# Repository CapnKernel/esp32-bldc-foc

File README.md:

# esp32-bldc-foc
A clone of the MKS ESP32-based FOC BLDC driver

Originally found here:

  https://github.com/makerbase-motor/MKS-ESP32FOC

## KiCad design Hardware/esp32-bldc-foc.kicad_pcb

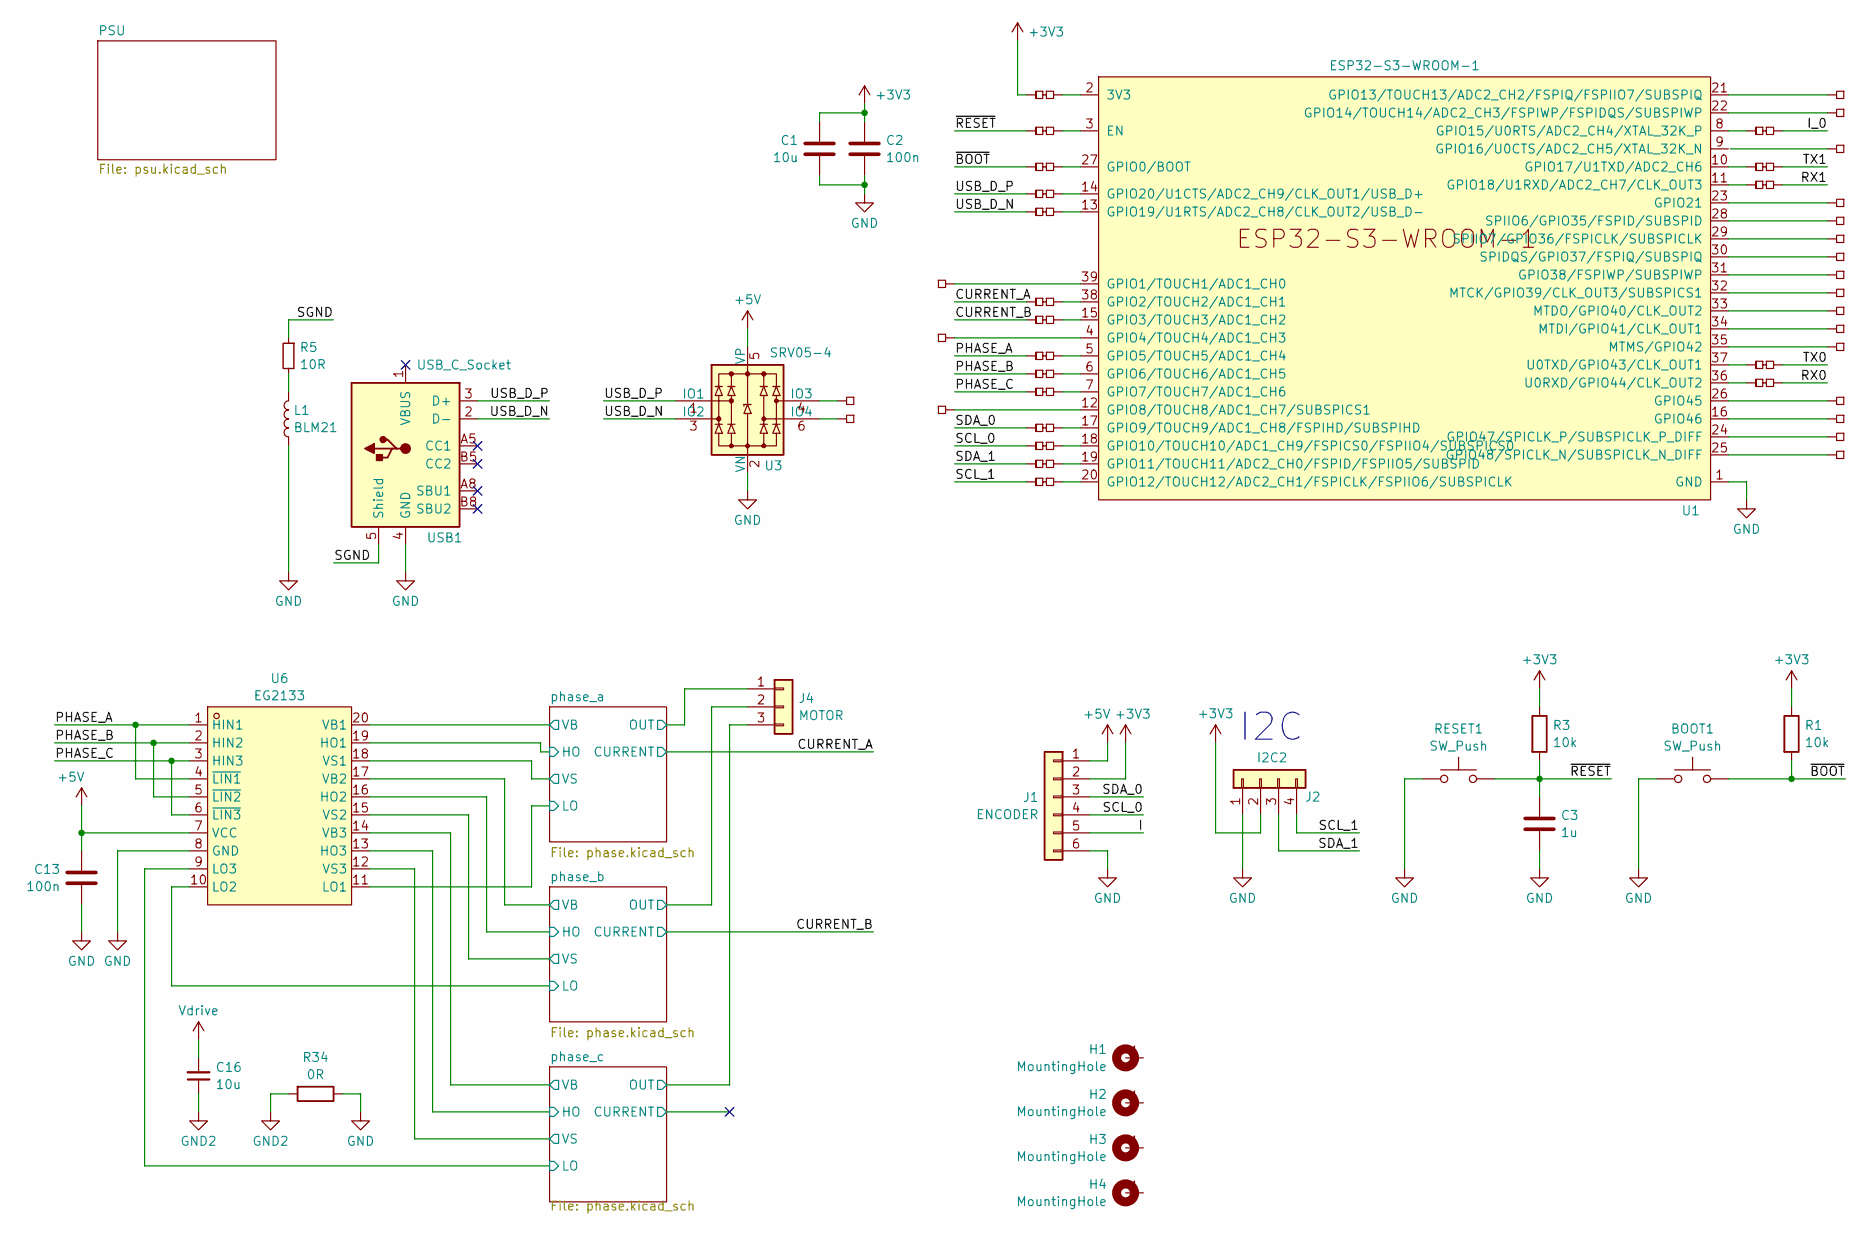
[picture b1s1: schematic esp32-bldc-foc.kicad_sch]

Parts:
BOOT1: SW_Push; SW_Push_SPST_NO_432
C1: 10u; C_0805_2012Metric
C2, C13: 100n; C_0603_1608Metric
C3: 1u; C_0603_1608Metric
C16: 10u; C_1206_3216Metric
H1, H2, H3, H4: MountingHole; MountingHole_3.2mm_M3_Pad
J1: ENCODER; PinSocket_1x06_P2.54mm_Vertical
J2: I2C2; JST_SH_SM04B-SRSS-TB_1x04-1MP_P1.00mm_Horizontal
J4: MOTOR; TerminalBlock_MetzConnect_Type094_RT03503HBLU_1x03_P5.00mm_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
L1: BLM21; L_0603_1608Metric
P1, P2, P3, P4, P5, P6, P7, P8, P9, P10, P11, P12, P13, P14, P15, P16, P17, P18, P19, P20, P21: PCB_Pin_Breakout; tinySJ-Testpoint-0.7mm
P22, P23, P24, P25, P26, P27, P28, P29, P30, P31, P32, P33, P34, P35, P36, P37, P38, P39, P40: PCB_Patch; tinySJ-Bridged
R1, R3: 10k; R_0603_1608Metric
R5: 10R; R_0603_1608Metric
R34: 0R; R_0805_2012Metric
RESET1: SW_Push; SW_Push_SPST_NO_432
U1: ESP32-S3-WROOM-1
U3: SRV05-4; SOT-23-6
U6: EG2133; TSSOP-20_L6.5-W4.4-P0.65-LS6.4-BL; LCSC C190343
USB1: USB_C_Socket; Tinker-USB_C; LCSC C2765186

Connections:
+3V3: C1.1, C2.1, J1.2, J2.2, P40.1, R1.1, R3.1; also elsewhere on the board
+5V: C13.2, J1.1, U3.5 (VP), U6.7 (VCC); also elsewhere on the board
/CURRENT_A: P26.1; also elsewhere on the board
/CURRENT_B: P27.1; also elsewhere on the board
/I: J1.5
/I_0: P35.2
/PHASE_A: P28.1, U6.1 (HIN1), U6.4 (~LIN1)
/PHASE_B: P29.1, U6.2 (HIN2), U6.5 (~LIN2)
/PHASE_C: P30.1, U6.3 (HIN3), U6.6 (~LIN3)
/RX0: P39.2
/RX1: P37.2
/SCL_0: J1.4, P32.1
/SCL_1: J2.4, P34.1
/SDA_0: J1.3, P31.1
/SDA_1: J2.3, P33.1
/SGND: R5.1, USB1.5 (Shield)
/TX0: P38.2
/TX1: P36.2
/USB_D_N: P25.1, U3.3 (IO2), USB1.2 (D-)
/USB_D_P: P24.1, U3.1 (IO1), USB1.3 (D+)
/phase_a/HO: U6.19 (HO1); also elsewhere on the board
/phase_a/LO: U6.11 (LO1); also elsewhere on the board
/phase_a/OUT: J4.1; also elsewhere on the board
/phase_a/VB: U6.20 (VB1); also elsewhere on the board
/phase_a/VS: U6.18 (VS1); also elsewhere on the board
/phase_b/HO: U6.16 (HO2); also elsewhere on the board
/phase_b/LO: U6.10 (LO2); also elsewhere on the board
/phase_b/OUT: J4.2; also elsewhere on the board
/phase_b/VB: U6.17 (VB2); also elsewhere on the board
/phase_b/VS: U6.15 (VS2); also elsewhere on the board
/phase_c/HO: U6.13 (HO3); also elsewhere on the board
/phase_c/LO: U6.9 (LO3); also elsewhere on the board
/phase_c/OUT: J4.3; also elsewhere on the board
/phase_c/VB: U6.14 (VB3); also elsewhere on the board
/phase_c/VS: U6.12 (VS3); also elsewhere on the board
/~BOOT: BOOT1.2, P23.1, R1.2
/~RESET: C3.1, P22.1, R3.2, RESET1.2
GND: BOOT1.1, C1.2, C2.2, C3.2, C13.1, J1.6, J2.1, L1.2, R34.1, RESET1.1, U1.1 (GND), U1.40 (GND), U1.41 (GND), U3.2 (VN), U6.8 (GND), USB1.4 (GND); also elsewhere on the board
GND2: C16.1, R34.2; also elsewhere on the board
unnamed: L1.1, R5.2
unnamed: P40.2, U1.2 (3V3)
unnamed: P22.2, U1.3 (EN)
unnamed: P23.2, U1.27 (GPIO0/BOOT)
unnamed: P1.1, U1.39 (GPIO1/TOUCH1/ADC1_CH0)
unnamed: P26.2, U1.38 (GPIO2/TOUCH2/ADC1_CH1)
unnamed: P27.2, U1.15 (GPIO3/TOUCH3/ADC1_CH2)
unnamed: P2.1, U1.4 (GPIO4/TOUCH4/ADC1_CH3)
unnamed: P28.2, U1.5 (GPIO5/TOUCH5/ADC1_CH4)
unnamed: P29.2, U1.6 (GPIO6/TOUCH6/ADC1_CH5)
unnamed: P30.2, U1.7 (GPIO7/TOUCH7/ADC1_CH6)
unnamed: P3.1, U1.12 (GPIO8/TOUCH8/ADC1_CH7/SUBSPICS1)
unnamed: P31.2, U1.17 (GPIO9/TOUCH9/ADC1_CH8/FSPIHD/SUBSPIHD)
unnamed: P32.2, U1.18 (GPIO10/TOUCH10/ADC1_CH9/FSPICS0/FSPIIO4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)
unnamed: P33.2, U1.19 (GPIO11/TOUCH11/ADC2_CH0/FSPID/FSPIIO5/S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)
unnamed: P34.2, U1.20 (GPIO12/TOUCH12/ADC2_CH1/FSPICLK/FSPIIO6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)
unnamed: P4.1, U1.21 (GPIO13/TOUCH13/ADC2_CH2/FSPIQ/FSPIIO7/S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)
unnamed: P5.1, U1.22 (GPIO14/TOUCH14/ADC2_CH3/FSPIWP/FSPIDQS/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)
unnamed: P35.1, U1.8 (GPIO15/U0RTS/ADC2_CH4/XTAL_32K_P)
unnamed: P36.1, U1.10 (GPIO17/U1TXD/ADC2_CH6)
unnamed: P37.1, U1.11 (GPIO18/U1RXD/ADC2_CH7/CLK_OUT3)
unnamed: P25.2, U1.13 (GPIO19/U1RTS/ADC2_CH8/CLK_OUT2/USB_D-)
unnamed: P24.2, U1.14 (GPIO20/U1CTS/ADC2_CH9/CLK_OUT1/USB_D+)
unnamed: P7.1, U1.23 (GPIO21)
unnamed: P11.1, U1.31 (GPIO38/FSPIWP/SUBSPIWP)
unnamed: P16.1, U1.26 (GPIO45)
unnamed: P17.1, U1.16 (GPIO46)
unnamed: P18.1, U1.24 (GPIO47/SPICLK_P/SUBSPICLK_P_DIFF)
unnamed: P19.1, U1.25 (GPIO48/SPICLK_N/SUBSPICLK_N_DIFF)
unnamed: P12.1, U1.32 (MTCK/GPIO39/CLK_OUT3/SUBSPICS1)
unnamed: P14.1, U1.34 (MTDI/GPIO41/CLK_OUT1)
unnamed: P13.1, U1.33 (MTDO/GPIO40/CLK_OUT2)
unnamed: P15.1, U1.35 (MTMS/GPIO42)
unnamed: P10.1, U1.30 (SPIDQS/GPIO37/FSPIQ/SUBSPIQ)
unnamed: P8.1, U1.28 (SPIIO6/GPIO35/FSPID/SUBSPID)
unnamed: P9.1, U1.29 (SPIIO7/GPIO36/FSPICLK/SUBSPICLK)
unnamed: P39.1, U1.36 (U0RXD/GPIO44/CLK_OUT2)
unnamed: P38.1, U1.37 (U0TXD/GPIO43/CLK_OUT1)
unnamed: P20.1, U3.4 (IO3)
unnamed: P21.1, U3.6 (IO4)
Vdrive: C16.2; also elsewhere on the board

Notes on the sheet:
I2C

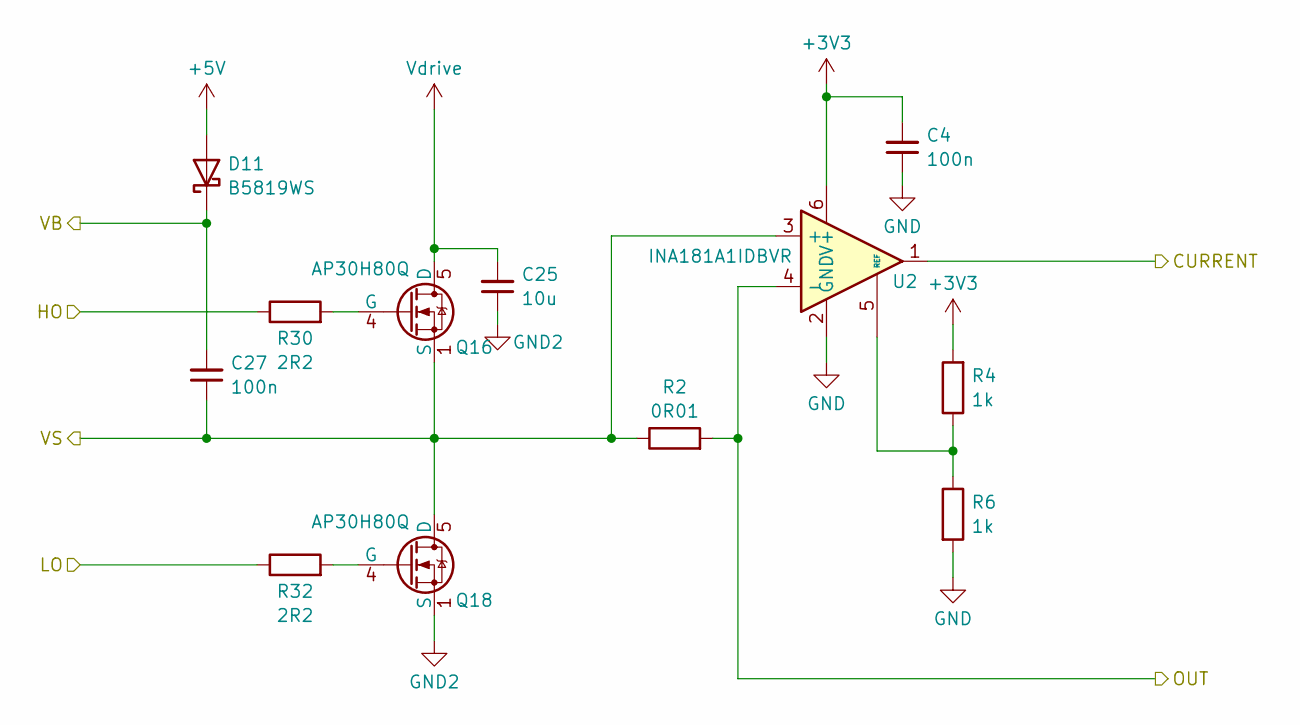
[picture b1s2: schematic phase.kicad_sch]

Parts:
C4, C27: 100n; C_0603_1608Metric
C25: 10u; C_1206_3216Metric
D11: B5819WS; D_SOD-323
Q16, Q18: AP30H80Q; DFN-8_L3.2-W3.1-P0.65-LS3.4-BL; LCSC C2828592
R2: 0R01; R_1206_3216Metric
R4, R6: 1k; R_0603_1608Metric
R30, R32: 2R2; R_0603_1608Metric
U2: INA181A1IDBVR; SOT-23-6; LCSC C2058943

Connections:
+3V3: C4.2, R4.2, U2.6 (V+); also elsewhere on the board
+5V: D11.2 (A); also elsewhere on the board
/phase_c/CURRENT: U2.1
/phase_c/HO: R30.1; also elsewhere on the board
/phase_c/LO: R32.1; also elsewhere on the board
/phase_c/OUT: R2.2, U2.4 (-); also elsewhere on the board
/phase_c/VB: C27.2, D11.1 (K); also elsewhere on the board
/phase_c/VS: C27.1, Q16.1 (S), Q16.2 (S), Q16.3 (S), Q18.5 (D), Q18.6 (D), Q18.7 (D), Q18.8 (D), Q18.9 (D), R2.1, U2.3 (+); also elsewhere on the board
GND: C4.1, R6.2, U2.2 (GND); also elsewhere on the board
GND2: C25.1, Q18.1 (S), Q18.2 (S), Q18.3 (S); also elsewhere on the board
unnamed: Q16.4 (G), R30.2
unnamed: Q18.4 (G), R32.2
unnamed: R4.1, R6.1, U2.5 (REF)
Vdrive: C25.2, Q16.5 (D), Q16.6 (D), Q16.7 (D), Q16.8 (D), Q16.9 (D); also elsewhere on the board

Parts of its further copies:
C15, C21: 10u; C_1206_3216Metric
C19, C23, C29, C30: 100n; C_0603_1608Metric
D7, D9: B5819WS; D_SOD-323
Q8, Q10, Q12, Q14: AP30H80Q; DFN-8_L3.2-W3.1-P0.65-LS3.4-BL; LCSC C2828592
R18, R22, R24, R28: 2R2; R_0603_1608Metric
R20, R26: 0R01; R_1206_3216Metric
R36, R37, R38, R39: 1k; R_0603_1608Metric
U21, U23: INA181A1IDBVR; SOT-23-6; LCSC C2058943

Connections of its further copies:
+3V3: C29.2, C30.2, R36.2, R38.2, U21.6 (V+), U23.6 (V+); also elsewhere on the board
+5V: D7.2 (A), D9.2 (A); also elsewhere on the board
/CURRENT_A: U21.1; also elsewhere on the board
/CURRENT_B: U23.1; also elsewhere on the board
/phase_a/HO: R18.1; also elsewhere on the board
/phase_a/LO: R22.1; also elsewhere on the board
/phase_a/OUT: R20.2, U21.4 (-); also elsewhere on the board
/phase_a/VB: C19.2, D7.1 (K); also elsewhere on the board
/phase_a/VS: C19.1, Q8.1 (S), Q8.2 (S), Q8.3 (S), Q10.5 (D), Q10.6 (D), Q10.7 (D), Q10.8 (D), Q10.9 (D), R20.1, U21.3 (+); also elsewhere on the board
/phase_b/HO: R24.1; also elsewhere on the board
/phase_b/LO: R28.1; also elsewhere on the board
/phase_b/OUT: R26.2, U23.4 (-); also elsewhere on the board
/phase_b/VB: C23.2, D9.1 (K); also elsewhere on the board
/phase_b/VS: C23.1, Q12.1 (S), Q12.2 (S), Q12.3 (S), Q14.5 (D), Q14.6 (D), Q14.7 (D), Q14.8 (D), Q14.9 (D), R26.1, U23.3 (+); also elsewhere on the board
GND: C29.1, C30.1, R37.2, R39.2, U21.2 (GND), U23.2 (GND); also elsewhere on the board
GND2: C15.1, C21.1, Q10.1 (S), Q10.2 (S), Q10.3 (S), Q14.1 (S), Q14.2 (S), Q14.3 (S); also elsewhere on the board
unnamed: Q8.4 (G), R18.2
unnamed: Q10.4 (G), R22.2
unnamed: Q12.4 (G), R24.2
unnamed: Q14.4 (G), R28.2
unnamed: R36.1, R37.1, U21.5 (REF)
unnamed: R38.1, R39.1, U23.5 (REF)
Vdrive: C15.2, C21.2, Q8.5 (D), Q8.6 (D), Q8.7 (D), Q8.8 (D), Q8.9 (D), Q12.5 (D), Q12.6 (D), Q12.7 (D), Q12.8 (D), Q12.9 (D); also elsewhere on the board

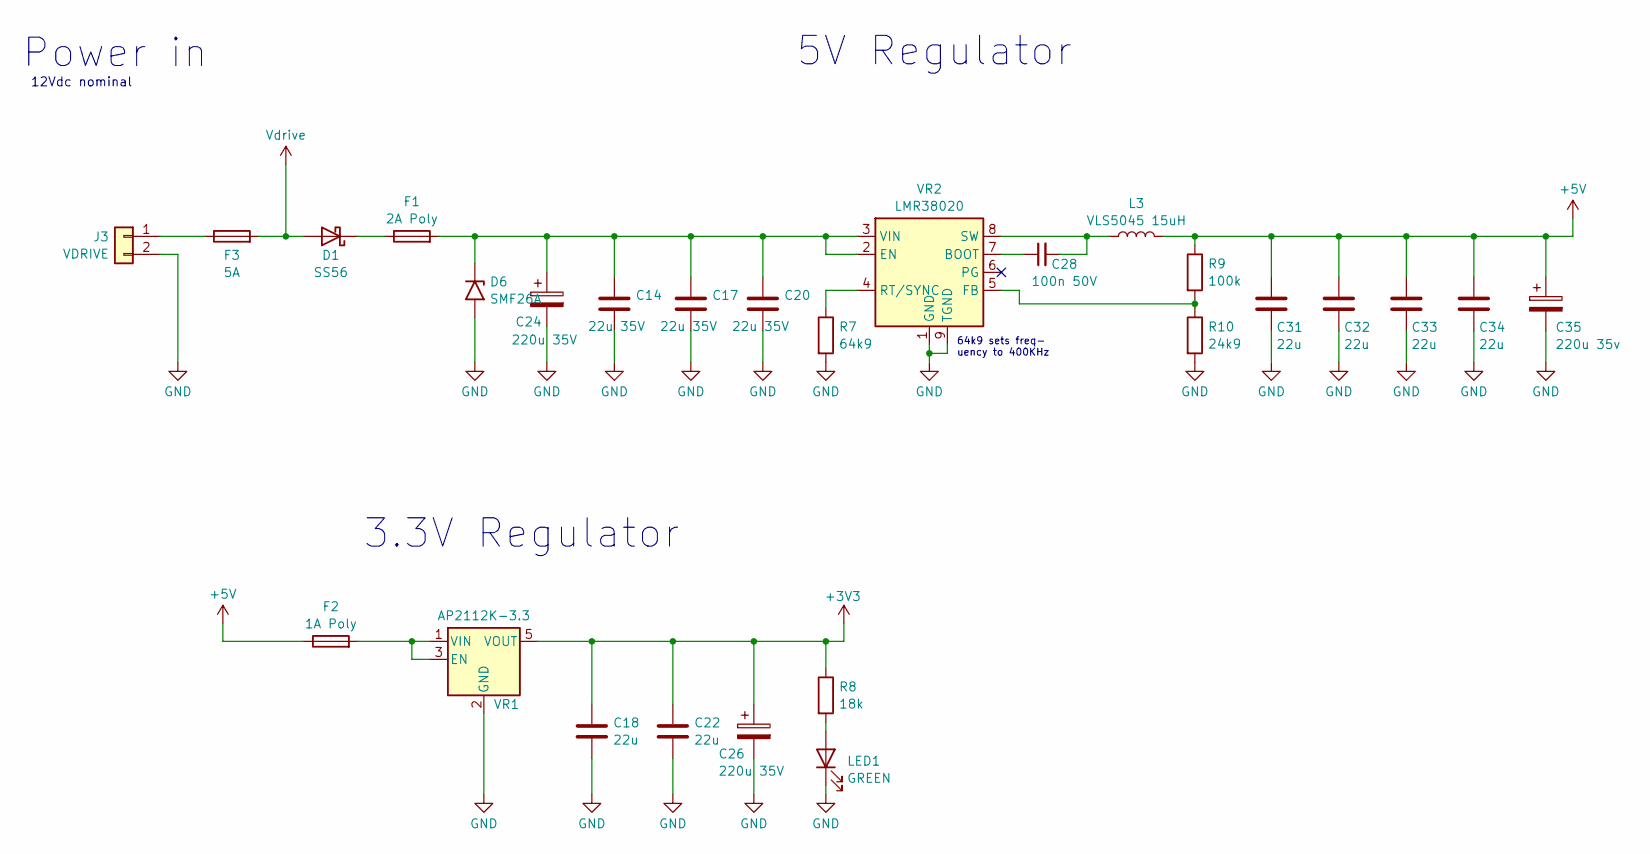
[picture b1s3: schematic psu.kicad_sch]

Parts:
C14, C17, C20: 22u 35V; C_0805_2012Metric
C18, C22, C31, C32, C33, C34: 22u; C_0805_2012Metric
C24, C26: 220u 35V; CP_Elec_8x10
C28: 100n 50V; C_0603_1608Metric
C35: 220u 35v; CP_Elec_8x10
D1: SS56; D_SMA
D6: SMF26A; D_SMF
F1: 2A Poly; Fuse_2018_5045Metric
F2: 1A Poly; Fuse_1206_3216Metric
F3: 5A; Fuseholder_Blade
J3: VDRIVE; TerminalBlock_MetzConnect_Type086_RT03402HBLC_1x02_P3.81mm_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
L3: VLS5045 15uH; L_TDK_VLS6045EX_VLS6045AF
LED1: GREEN; LED_0603_1608Metric
R7: 64k9; R_0603_1608Metric
R8: 18k; R_0603_1608Metric
R9: 100k; R_0603_1608Metric
R10: 24k9; R_0603_1608Metric
VR1: AP2112K-3.3; SOT-23-5
VR2: LMR38020; Texas_HSOP-8-1EP_3.9x4.9mm_P1.27mm_ThermalVias

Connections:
+3V3: C18.1, C22.1, C26.1, R8.1, VR1.5 (VOUT); also elsewhere on the board
+5V: C31.1, C32.1, C33.1, C34.1, C35.1, F2.1, L3.2, R9.1; also elsewhere on the board
GND: C14.2, C17.2, C18.2, C20.2, C22.2, C24.2, C26.2, C31.2, C32.2, C33.2, C34.2, C35.2, D6.2 (A2), J3.2, LED1.1 (K), R7.2, R10.2, VR1.2 (GND), VR2.1 (GND), VR2.9 (TGND); also elsewhere on the board
unnamed: D1.1 (K), F1.1
unnamed: C14.1, C17.1, C20.1, C24.1, D6.1 (A1), F1.2, VR2.2 (EN), VR2.3 (VIN)
unnamed: F3.1, J3.1
unnamed: LED1.2 (A), R8.2
unnamed: F2.2, VR1.1 (VIN), VR1.3 (EN)
unnamed: C28.1, VR2.7 (BOOT)
unnamed: R9.2, R10.1, VR2.5 (FB)
unnamed: R7.1, VR2.4 (RT/SYNC)
unnamed: C28.2, L3.1, VR2.8 (SW)
Vdrive: D1.2 (A), F3.2; also elsewhere on the board

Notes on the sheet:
12Vdc nominal
5V Regulator
3.3V Regulator
Power in
64k9 sets freq- uency to 400KHz

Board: 4 copper layers, 126 parts (17 on the bottom side), 92 nets, no tracks yet.

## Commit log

2024-08-07 Added most components to the schematic, including symbols lifted from LCSC
2024-08-07 First cut of power regulation wiring
2024-08-07 Placed all components
2024-08-07 Reannotated
2024-08-08 Swapped some pins to allow for CURRENT3 if we need it.
2024-08-08 Moved afork-kicad-parts to Hardware subdir
2024-08-08 Pretty much all components now have values
2024-08-08 Add jumpers to ESP32-S3
2024-08-08 First cut of PCB (early parts)
2024-08-08 Second cut of circuit board
2024-08-08 Third cut of PCB. Ready for BoM and routing
2024-08-08 Remove "LCSC Part" field (I use just "LCSC")
2024-08-09 Replaced power supply with the one from OpenKayo
